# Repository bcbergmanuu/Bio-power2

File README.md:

Design goals:  

LDO:  [lt3041](https://www.analog.com/en/products/lt3041.html)
   1. High PSRR as to reduce powerpack boost converter noise
   2. Low dropout to extend powerpack life (current 310mv)
   3. Low RMS noise
   4. 1A output capability
   5. DC 6.2 volt

Power Delivery: [stusb4500](https://www.st.com/en/interfaces-and-transceivers/stusb4500.html)
   1. Power delivery 3 capability to reduce power consumption.
   2. PD2 will be set to 9 volt, loss ~50%
   3. PD3 will be set to 6.6v volt, loss <10%.    

PCB Design:

Schematics:

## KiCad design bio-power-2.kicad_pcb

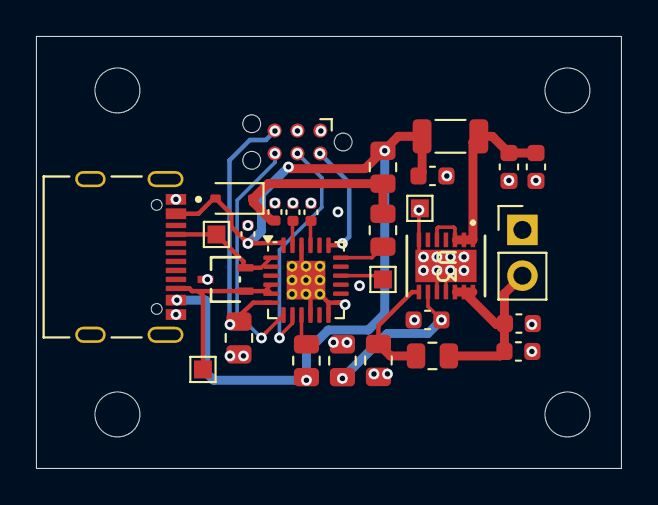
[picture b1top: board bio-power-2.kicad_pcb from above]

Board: 4 copper layers, 32.5 x 24.0 mm, 33 parts (0 on the bottom side), 18 nets.

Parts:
C1, C2, C3, C7: 1u; C_0402_1005Metric
C4, C5, C6, C8, C9, C11: 10u; C_0603_1608Metric
CR1: ESDA25W; SOT323-3L_STM
D1: D_Schottky; D_SOD-323
FB1: YI321611U151-4R5T; L_1206_3216Metric
H1, H2, H3, H4: MountingHole; MountingHole_2.5mm
J1: TYPE-C-31-M-12; HRO_TYPE-C-31-M-12
J2: 6vdc; PinHeader_1x02_P2.54mm_Vertical
J3: TC2030-IDC; Tag-Connect_TC2030-IDC-NL_2x03_P1.27mm_Vertical
R1: 100k; R_0805_2012Metric
R3, R7: 1k; R_0805_2012Metric
R4: 470; R_0805_2012Metric
R9: 1M; R_0805_2012Metric
R10: 51k; R_0805_2012Metric
R11: 62k; R_0805_2012Metric
TP1: cc2; TestPoint_Pad_1.0x1.0mm
TP2: gnd; TestPoint_Pad_1.0x1.0mm
TP3: VBUS_EN; TestPoint_Pad_1.0x1.0mm
TP4: cc1; TestPoint_Pad_1.0x1.0mm
U1: STUSB4500QTR; QFN-24-1EP_4x4mm_P0.5mm_EP2.15x2.15mm_ThermalVias
U3: LT3041ADE-PBF; 05-08-1708_ADI

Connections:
9v: C4.1, C5.1, FB1.2, U3.1 (IN), U3.2 (IN), U3.3 (IN), U3.5 (EN/UV)
+6V2: C6.1, C9.1, J2.2, R9.1, U3.12 (OUTS), U3.13 (OUT), U3.14 (OUT)
/ALERT: J3.2, U1.19 (ALERT)
/CC1: CR1.2, J1.A5 (CC1), TP4.1, U1.1 (CC1DB), U1.2 (CC1)
/CC2: CR1.1, J1.B5 (CC2), TP1.1, U1.4 (CC2), U1.5 (CC2DB)
/RESET: J3.5, R1.2, U1.6 (RESET)
/SCL: J3.6, U1.7 (SCL)
/SDA: J3.4, U1.8 (SDA)
GND: C1.2, C2.2, C3.2, C4.2, C5.2, C6.2, C7.1, C8.2, C9.2, C11.2, CR1.3, J1.A1_B12 (GND), J1.B1_A12 (GND), J1.S1 (SHIELD), J1.S2 (SHIELD), J1.S3 (SHIELD), J1.S4 (SHIELD), J2.1, J3.1, J3.3, R1.1, R10.2, R11.2, TP2.1, U1.10 (GND), U1.12 (ADDR0), U1.13 (ADDR1), U1.22 (VSYS), U1.25 (GND), U3.7 (ILIM), U3.10 (GND), U3.11 (GND), U3.15 (GND)
unnamed: C7.2, C8.1, D1.2 (A), FB1.1, J1.A4_B9 (VBUS), J1.B4_A9 (VBUS), R4.1, R7.1, U1.24 (VDD)
unnamed: C1.1, D1.1 (K), R3.1, R4.2
unnamed: R7.2, U1.9 (DISCH)
unnamed: TP3.1, U1.16 (VBUS_EN_SNK)
unnamed: R3.2, U1.18 (VBUS_VS_DISCH)
unnamed: C2.1, U1.21 (VREG_1V2)
unnamed: C3.1, U1.23 (VREG_2V7)
unnamed: R9.2, R10.1, U3.8 (PGFB)
unnamed: C11.1, R11.1, U3.9 (SET)

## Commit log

2024-06-06 first
2024-06-09 new symbols
2024-06-09 finish
2024-08-01 pictures add
2025-04-24 Update stusb4500.ino
    adjusted minimum and maximum voltages 5-20 for each pdo
